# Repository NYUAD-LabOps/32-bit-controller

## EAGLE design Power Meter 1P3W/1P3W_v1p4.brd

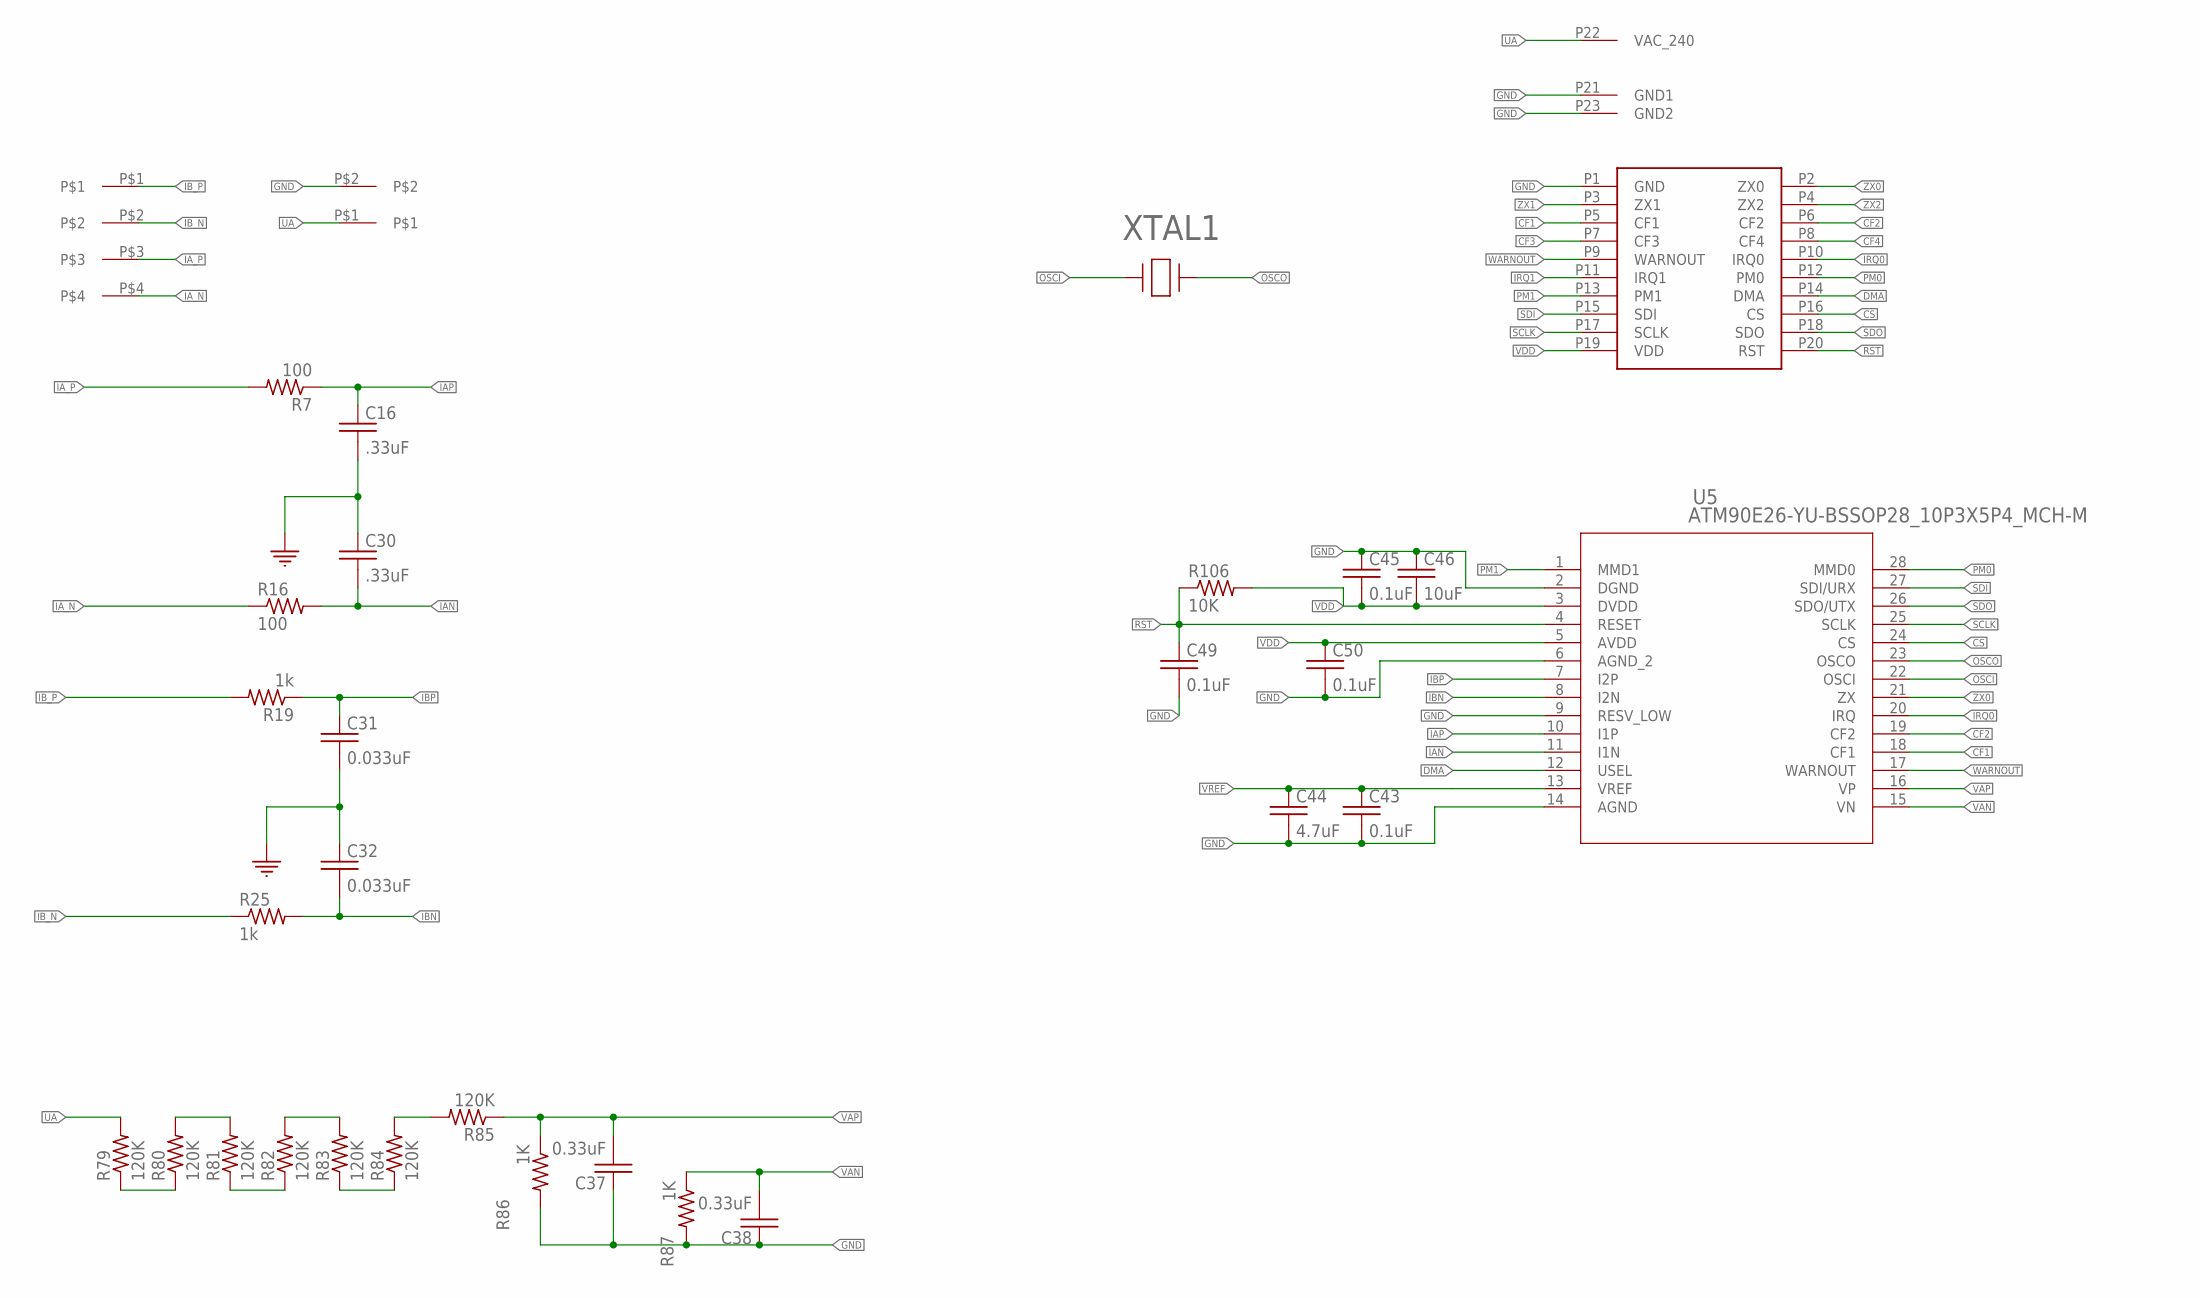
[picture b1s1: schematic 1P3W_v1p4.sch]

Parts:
C16, C30: .33uF; 0402
C31, C32: 0.033uF; 0402
C37, C38: 0.33uF; 0402
C43, C45, C49, C50: 0.1uF; 0402
C44: 4.7uF; 0402
C46: 10uF; 0402
J2: 3.81MM_1_X_4_RT_ANGLE_PLUG_HEADER; 1X4_3.81MM_PITCH
J3: 3.81MM_1_X_2_RT_ANGLE_PLUG_HEADER; 2_3.81MM_PITCH
R7, R16: 100; 0402
R19, R25: 1k; 0402
R79, R80, R81, R82, R83, R84, R85: 120K; 0402
R86, R87: 1K; 0402
R106: 10K; 0402
U5: ATM90E26-YU-BSSOP28_10P3X5P4_MCH-M; SSOP28_10P3X5P4_MCH-M
U$1: METER_BASE
XTAL1: ABLS-8.192MHZ-B2-TXTAL_HC/49US_ABLS_ABR-M; XTAL_HC/49US_ABLS_ABR-M

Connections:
CF1: U5.18 (CF1), U$1.P5 (CF1)
CF2: U5.19 (CF2), U$1.P6 (CF2)
CF3: U$1.P7 (CF3)
CF4: U$1.P8 (CF4)
CS: U5.24 (CS), U$1.P16 (CS)
DMA: U5.12 (USEL), U$1.P14 (DMA)
GND: C16.P$2 (2), C30.P$1 (1), C31.P$2 (2), C32.P$1 (1), C37.P$1 (1), C38.P$1 (1), C43.P$2 (2), C44.P$2 (2), C45.P$1 (1), C46.P$1 (1), C49.P$2 (2), C50.P$2 (2), J3.P$2, R86.P$2 (2), R87.P$2 (2), U5.2 (DGND), U5.6 (AGND_2), U5.9 (RESV_LOW), U5.14 (AGND), U$1.P1 (GND), U$1.P21 (GND1), U$1.P23 (GND2)
IAN: C30.P$2 (2), R16.P$2 (2), U5.11 (I1N)
IAP: C16.P$1 (1), R7.P$1 (1), U5.10 (I1P)
IA_N: J2.P$4, R16.P$1 (1)
IA_P: J2.P$3, R7.P$2 (2)
IBN: C32.P$2 (2), R25.P$2 (2), U5.8 (I2N)
IBP: C31.P$1 (1), R19.P$1 (1), U5.7 (I2P)
IB_N: J2.P$2, R25.P$1 (1)
IB_P: J2.P$1, R19.P$2 (2)
IRQ0: U5.20 (IRQ), U$1.P10 (IRQ0)
IRQ1: U$1.P11 (IRQ1)
unnamed: R79.P$1 (1), R80.P$1 (1)
unnamed: R80.P$2 (2), R81.P$2 (2)
unnamed: R81.P$1 (1), R82.P$1 (1)
unnamed: R82.P$2 (2), R83.P$2 (2)
unnamed: R83.P$1 (1), R84.P$1 (1)
unnamed: R84.P$2 (2), R85.P$2 (2)
OSCI: U5.22 (OSCI), XTAL1.1
OSCO: U5.23 (OSCO), XTAL1.2
PM0: U5.28 (MMD0), U$1.P12 (PM0)
PM1: U5.1 (MMD1), U$1.P13 (PM1)
RST: C49.P$1 (1), R106.P$1 (1), U5.4 (RESET), U$1.P20 (RST)
SCLK: U5.25 (SCLK), U$1.P17 (SCLK)
SDI: U5.27 (SDI/URX), U$1.P15 (SDI)
SDO: U5.26 (SDO/UTX), U$1.P18 (SDO)
UA: J3.P$1, R79.P$2 (2), U$1.P22 (VAC_240)
VAN: C38.P$2 (2), R87.P$1 (1), U5.15 (VN)
VAP: C37.P$2 (2), R85.P$1 (1), R86.P$1 (1), U5.16 (VP)
VDD: C45.P$2 (2), C46.P$2 (2), C50.P$1 (1), R106.P$2 (2), U5.3 (DVDD), U5.5 (AVDD), U$1.P19 (VDD)
VREF: C43.P$1 (1), C44.P$1 (1), U5.13 (VREF)
WARNOUT: U5.17 (WARNOUT), U$1.P9 (WARNOUT)
ZX0: U5.21 (ZX), U$1.P2 (ZX0)
ZX1: U$1.P3 (ZX1)
ZX2: U$1.P4 (ZX2)

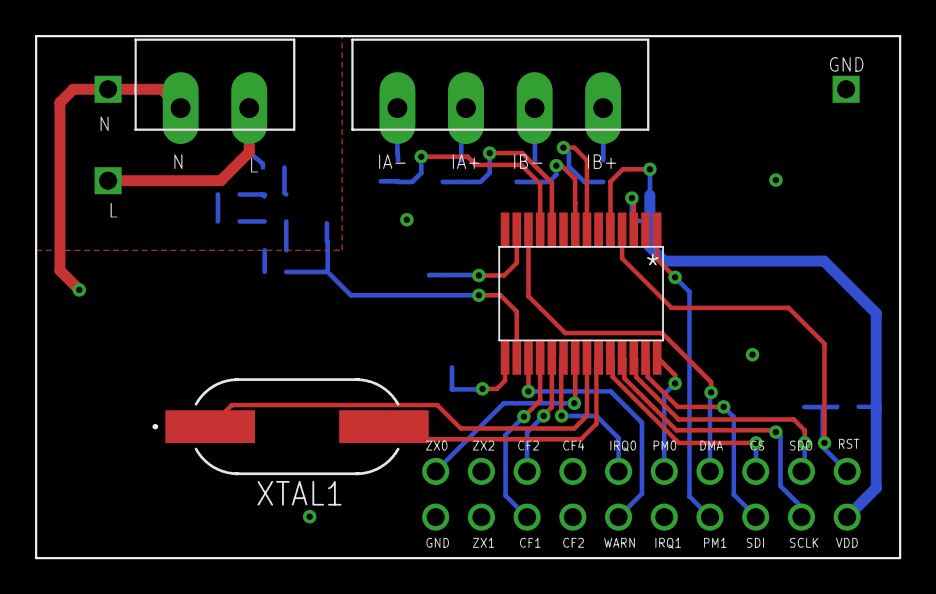
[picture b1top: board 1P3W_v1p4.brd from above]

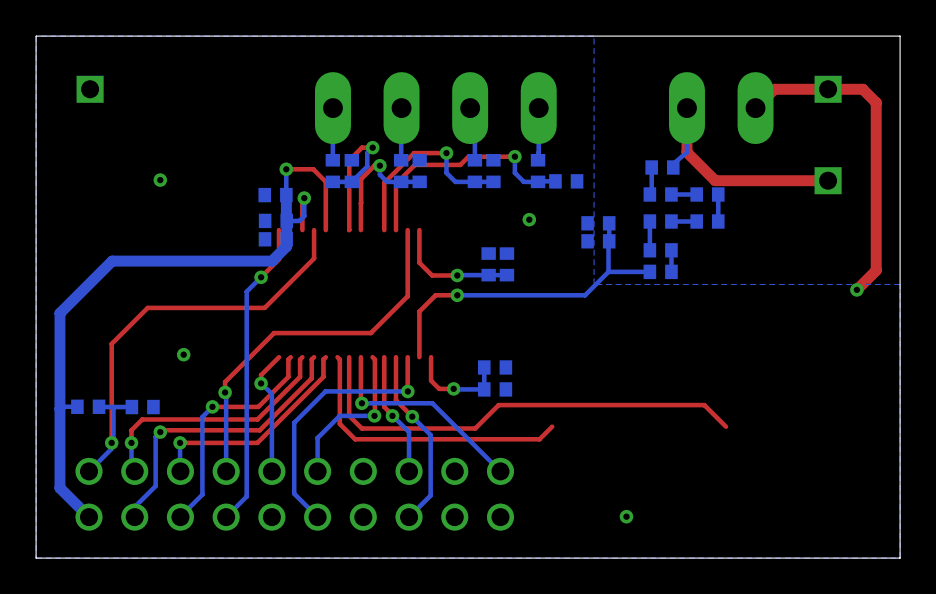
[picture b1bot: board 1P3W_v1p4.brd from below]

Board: 2 copper layers, 48.0 x 29.0 mm, 31 parts (26 on the bottom side), 35 nets.

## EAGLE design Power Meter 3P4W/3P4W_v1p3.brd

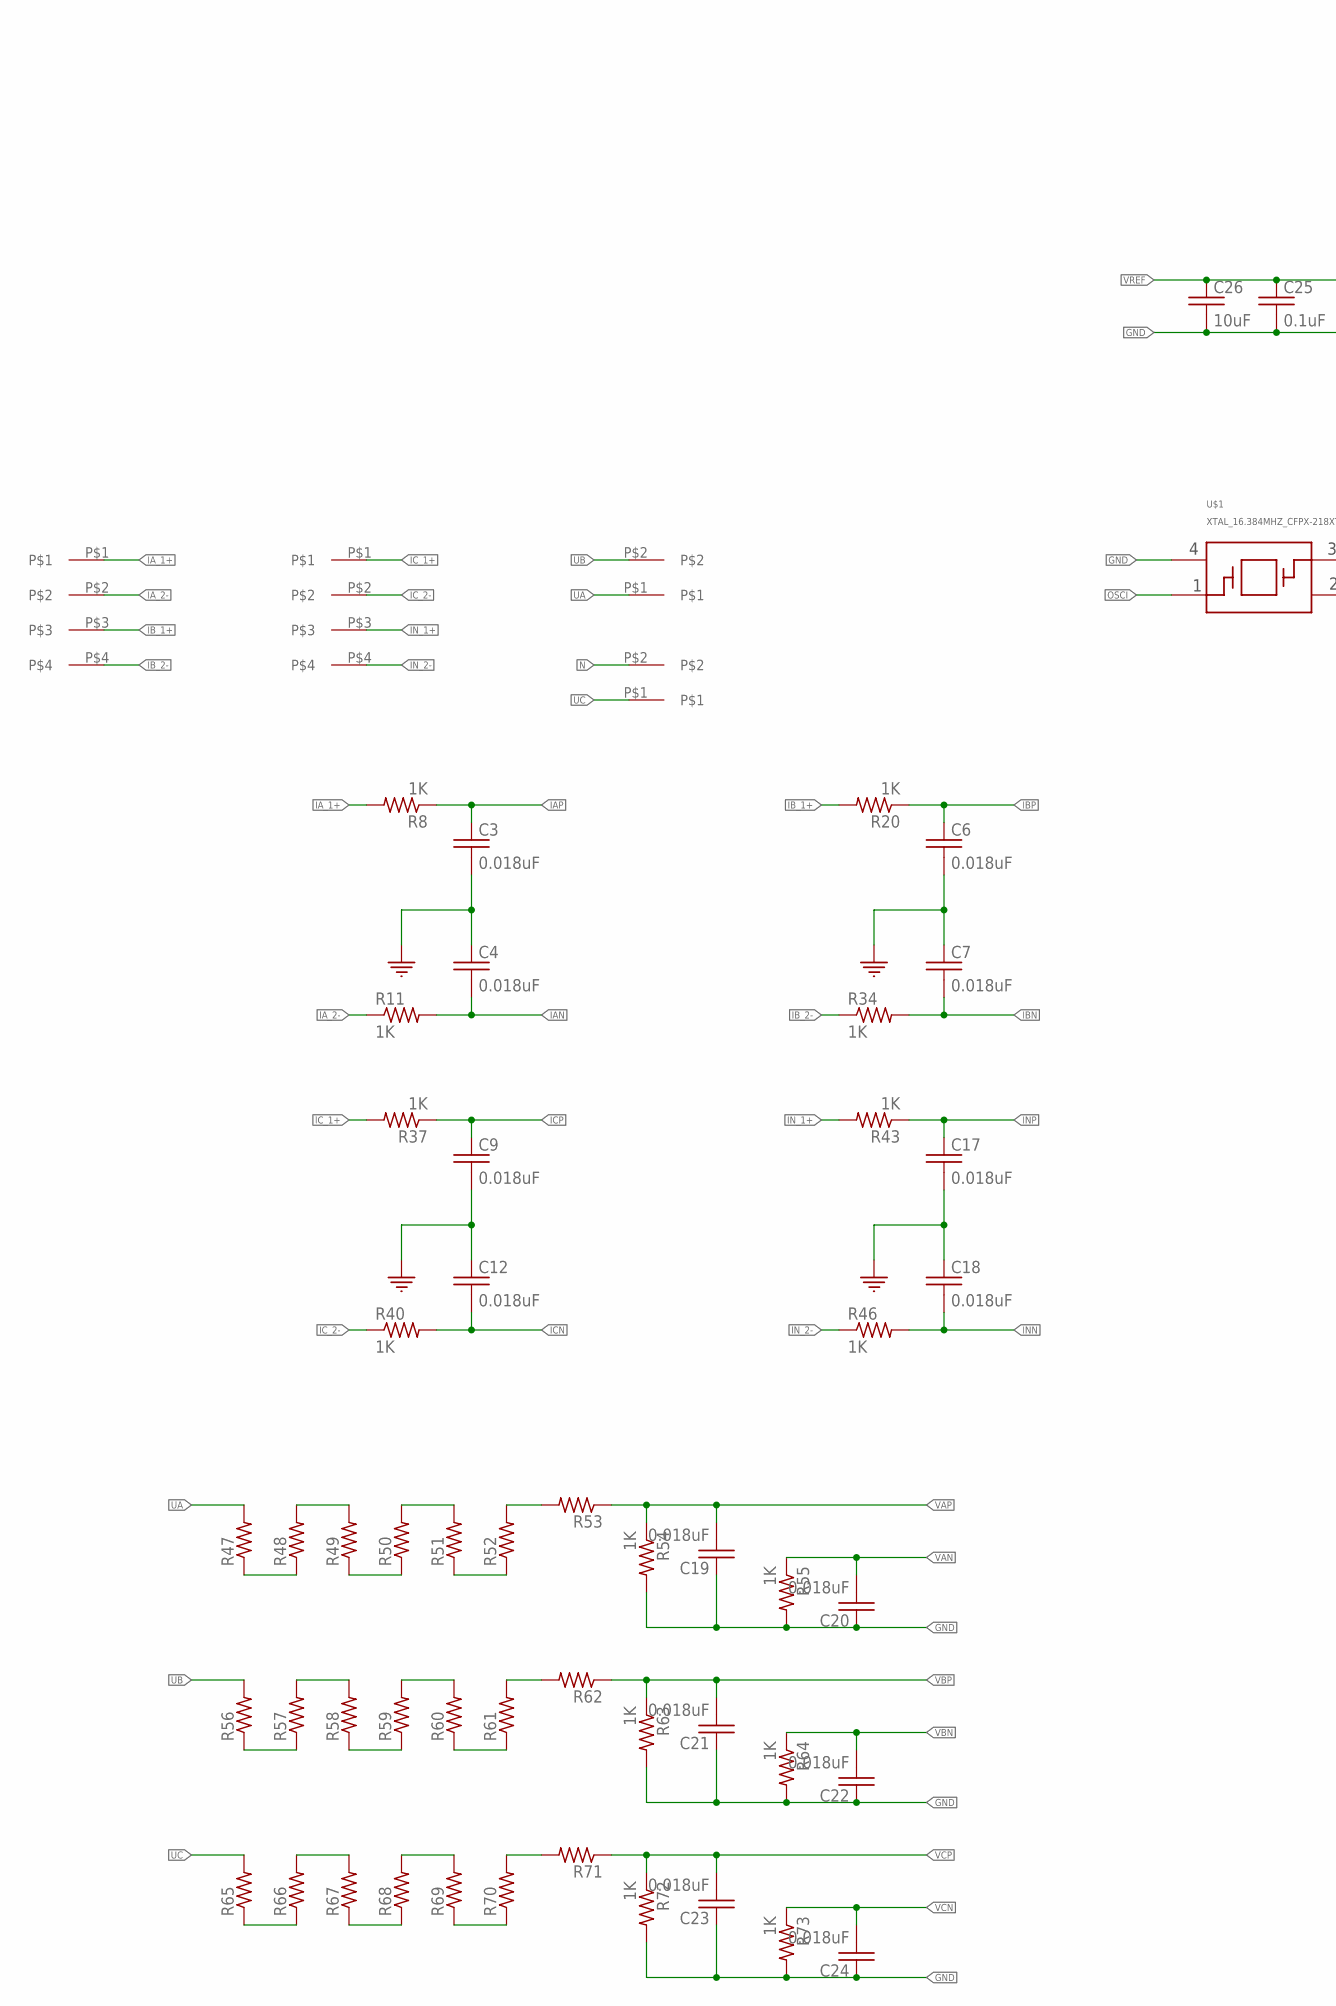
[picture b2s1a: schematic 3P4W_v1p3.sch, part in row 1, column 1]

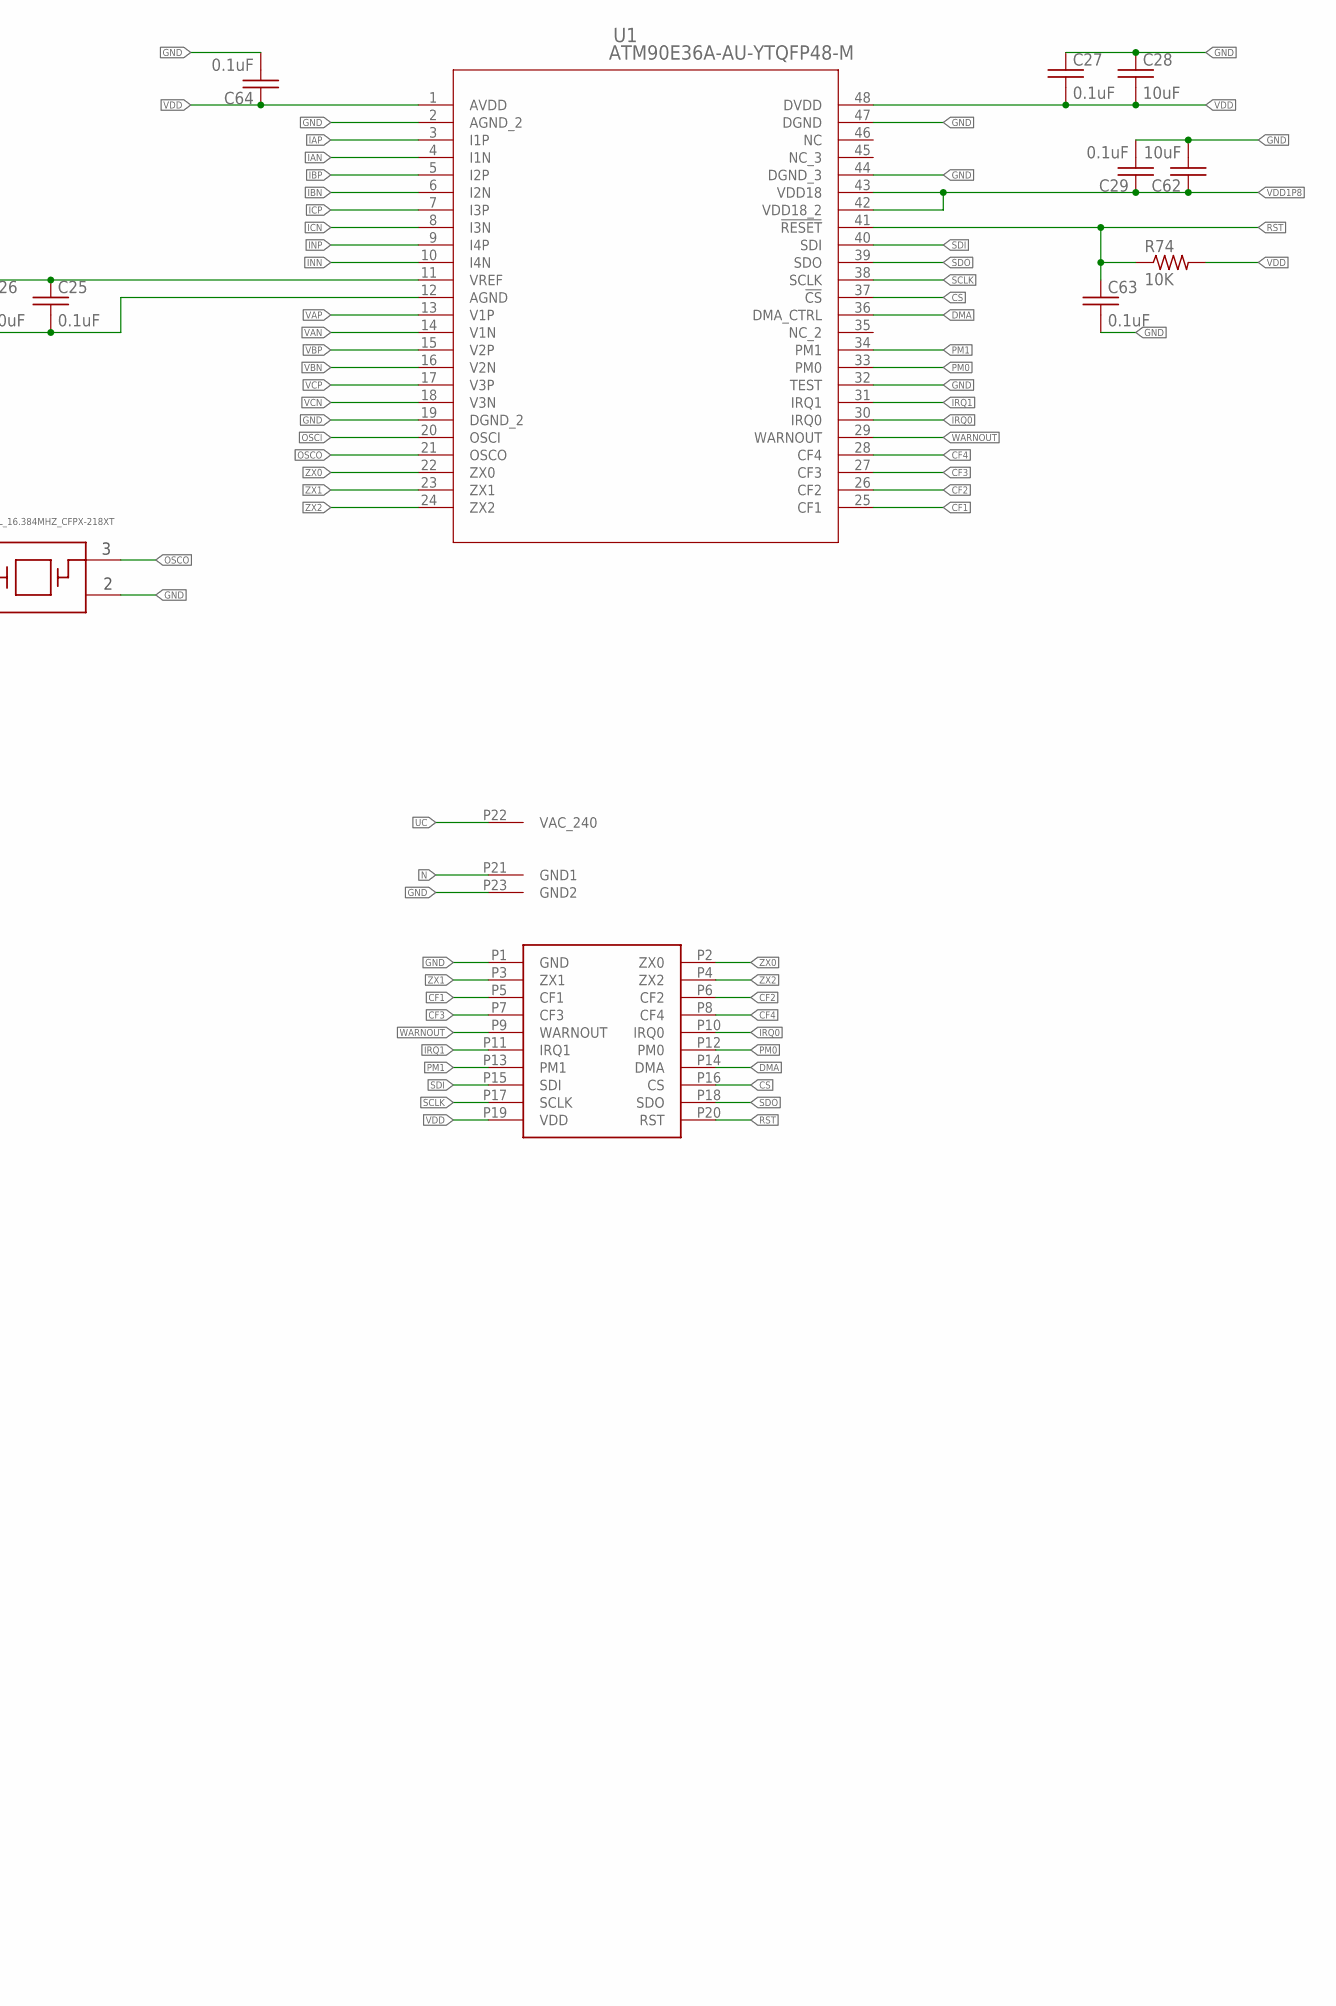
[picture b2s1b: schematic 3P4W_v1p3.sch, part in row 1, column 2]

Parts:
C3, C4, C6, C7, C9, C12, C17, C18, C19, C20, C21, C22, C23, C24: 0.018uF; 0402
C25, C27, C29, C63, C64: 0.1uF; 0402
C26, C28, C62: 10uF; 0402
J6, J7: 3.81MM_1_X_2_RT_ANGLE_PLUG_HEADER; 2_3.81MM_PITCH
J13, J14: 3.81MM_1_X_4_RT_ANGLE_PLUG_HEADER; 1X4_3.81MM_PITCH
R8, R11, R20, R34, R37, R40, R43, R46, R54, R55, R63, R64, R72, R73: 1K; 0402
R47, R48, R49, R50, R51, R52, R53, R56, R57, R58, R59, R60, R61, R62, R65, R66, R67, R68, R69, R70, R71: R_0402; 0402
R74: 10K; 0402
U1: ATM90E36A-AU-YTQFP48-M; TQFP48-M
U$1: XTAL_16.384MHZ_CFPX-218XT; XTAL_2.5X2.0
U$2: METER_BASE

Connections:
CF1: U1.25 (CF1), U$2.P5 (CF1)
CF2: U1.26 (CF2), U$2.P6 (CF2)
CF3: U1.27 (CF3), U$2.P7 (CF3)
CF4: U1.28 (CF4), U$2.P8 (CF4)
CS: U1.37 (!CS), U$2.P16 (CS)
DMA: U1.36 (DMA_CTRL), U$2.P14 (DMA)
GND: C3.P$2 (2), C4.P$1 (1), C6.P$2 (2), C7.P$1 (1), C9.P$2 (2), C12.P$1 (1), C17.P$2 (2), C18.P$1 (1), C19.P$1 (1), C20.P$1 (1), C21.P$1 (1), C22.P$1 (1), C23.P$1 (1), C24.P$1 (1), C25.P$2 (2), C26.P$2 (2), C27.P$1 (1), C28.P$1 (1), C29.P$2 (2), C62.P$2 (2), C63.P$2 (2), C64.P$2 (2), R54.P$2 (2), R55.P$2 (2), R63.P$2 (2), R64.P$2 (2), R72.P$2 (2), R73.P$2 (2), U1.2 (AGND_2), U1.12 (AGND), U1.19 (DGND_2), U1.32 (TEST), U1.44 (DGND_3), U1.47 (DGND), U$1.2, U$1.4, U$2.P1 (GND), U$2.P23 (GND2)
IAN: C4.P$2 (2), R11.P$2 (2), U1.4 (I1N)
IAP: C3.P$1 (1), R8.P$1 (1), U1.3 (I1P)
IA_1+: J13.P$1, R8.P$2 (2)
IA_2-: J13.P$2, R11.P$1 (1)
IBN: C7.P$2 (2), R34.P$2 (2), U1.6 (I2N)
IBP: C6.P$1 (1), R20.P$1 (1), U1.5 (I2P)
IB_1+: J13.P$3, R20.P$2 (2)
IB_2-: J13.P$4, R34.P$1 (1)
ICN: C12.P$2 (2), R40.P$2 (2), U1.8 (I3N)
ICP: C9.P$1 (1), R37.P$1 (1), U1.7 (I3P)
IC_1+: J14.P$1, R37.P$2 (2)
IC_2-: J14.P$2, R40.P$1 (1)
INN: C18.P$2 (2), R46.P$2 (2), U1.10 (I4N)
INP: C17.P$1 (1), R43.P$1 (1), U1.9 (I4P)
IN_1+: J14.P$3, R43.P$2 (2)
IN_2-: J14.P$4, R46.P$1 (1)
IRQ0: U1.30 (IRQ0), U$2.P10 (IRQ0)
IRQ1: U1.31 (IRQ1), U$2.P11 (IRQ1)
N: J7.P$2, U$2.P21 (GND1)
unnamed: R56.P$1 (1), R57.P$1 (1)
unnamed: R47.P$1 (1), R48.P$1 (1)
unnamed: R48.P$2 (2), R49.P$2 (2)
unnamed: R49.P$1 (1), R50.P$1 (1)
unnamed: R50.P$2 (2), R51.P$2 (2)
unnamed: R51.P$1 (1), R52.P$1 (1)
unnamed: R52.P$2 (2), R53.P$2 (2)
unnamed: R57.P$2 (2), R58.P$2 (2)
unnamed: R58.P$1 (1), R59.P$1 (1)
unnamed: R59.P$2 (2), R60.P$2 (2)
unnamed: R60.P$1 (1), R61.P$1 (1)
unnamed: R61.P$2 (2), R62.P$2 (2)
unnamed: R65.P$1 (1), R66.P$1 (1)
unnamed: R66.P$2 (2), R67.P$2 (2)
unnamed: R67.P$1 (1), R68.P$1 (1)
unnamed: R68.P$2 (2), R69.P$2 (2)
unnamed: R69.P$1 (1), R70.P$1 (1)
unnamed: R70.P$2 (2), R71.P$2 (2)
OSCI: U1.20 (OSCI), U$1.1
OSCO: U1.21 (OSCO), U$1.3
PM0: U1.33 (PM0), U$2.P12 (PM0)
PM1: U1.34 (PM1), U$2.P13 (PM1)
RST: C63.P$1 (1), R74.P$1 (1), U1.41 (!RESET), U$2.P20 (RST)
SCLK: U1.38 (SCLK), U$2.P17 (SCLK)
SDI: U1.40 (SDI), U$2.P15 (SDI)
SDO: U1.39 (SDO), U$2.P18 (SDO)
UA: J6.P$1, R47.P$2 (2)
UB: J6.P$2, R56.P$2 (2)
UC: J7.P$1, R65.P$2 (2), U$2.P22 (VAC_240)
VAN: C20.P$2 (2), R55.P$1 (1), U1.14 (V1N)
VAP: C19.P$2 (2), R53.P$1 (1), R54.P$1 (1), U1.13 (V1P)
VBN: C22.P$2 (2), R64.P$1 (1), U1.16 (V2N)
VBP: C21.P$2 (2), R62.P$1 (1), R63.P$1 (1), U1.15 (V2P)
VCN: C24.P$2 (2), R73.P$1 (1), U1.18 (V3N)
VCP: C23.P$2 (2), R71.P$1 (1), R72.P$1 (1), U1.17 (V3P)
VDD: C27.P$2 (2), C28.P$2 (2), C64.P$1 (1), R74.P$2 (2), U1.1 (AVDD), U1.48 (DVDD), U$2.P19 (VDD)
VDD1P8: C29.P$1 (1), C62.P$1 (1), U1.42 (VDD18_2), U1.43 (VDD18)
VREF: C25.P$1 (1), C26.P$1 (1), U1.11 (VREF)
WARNOUT: U1.29 (WARNOUT), U$2.P9 (WARNOUT)
ZX0: U1.22 (ZX0), U$2.P2 (ZX0)
ZX1: U1.23 (ZX1), U$2.P3 (ZX1)
ZX2: U1.24 (ZX2), U$2.P4 (ZX2)

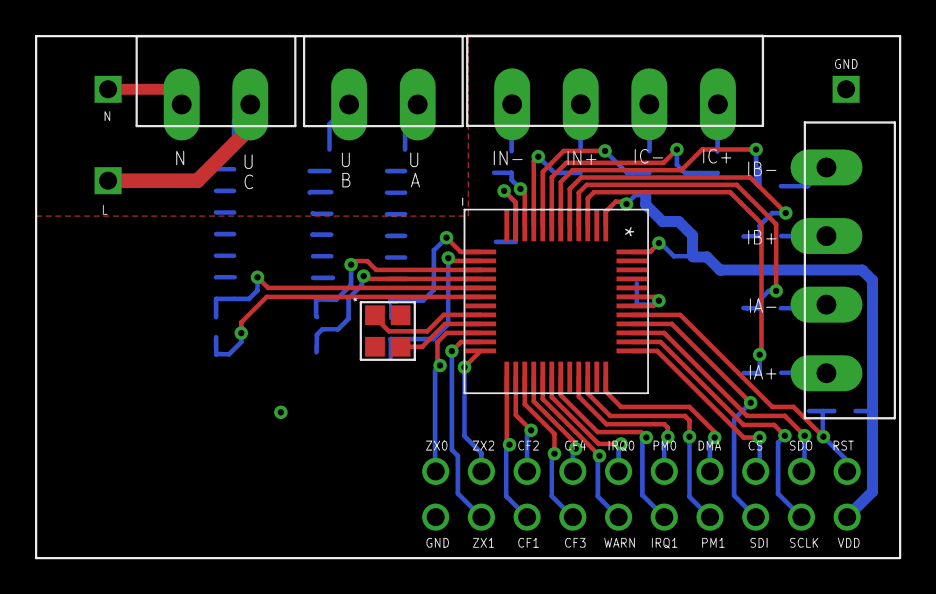
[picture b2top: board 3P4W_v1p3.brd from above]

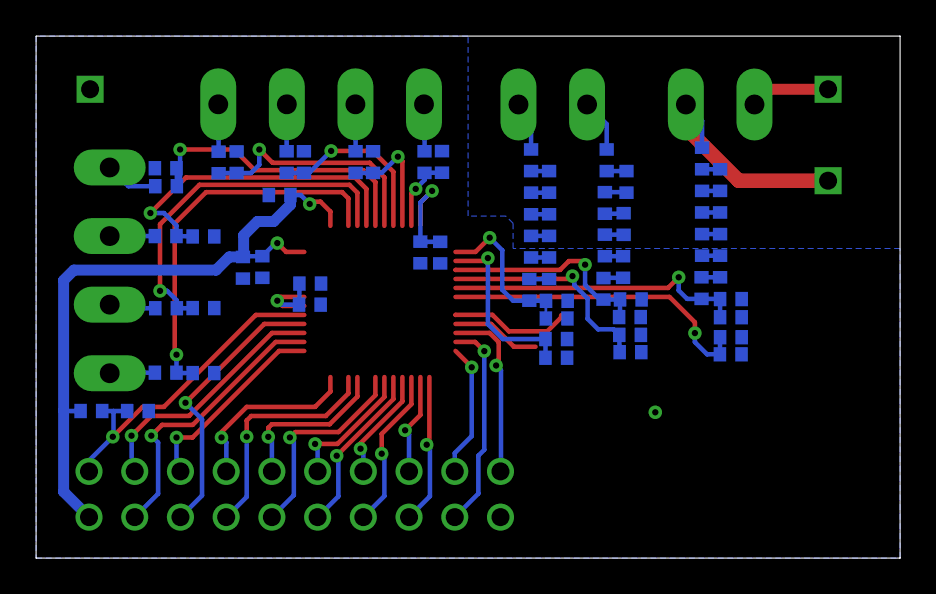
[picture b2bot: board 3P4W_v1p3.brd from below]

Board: 2 copper layers, 48.0 x 29.0 mm, 65 parts (58 on the bottom side), 68 nets.

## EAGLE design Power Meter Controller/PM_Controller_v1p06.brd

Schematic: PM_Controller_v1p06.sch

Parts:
C1, C3, C4, C6, C7, C8, C10, C11, C13, C14, C16, C17, C18, C19, C22, C24, C25, C27, C30, C31, C34, C35, C36, C37, C38, C39, C40, C44, C46, C49, C54, C55, C56, C58, C59, C60, C61, C62: 0.1uF; 0402
C2, C32, C65: 1uF; 0402
C5, C21, C29, C57, C63, C64: 10uF; 0402
C12, C33: 1.0 uF; 0402
C15: 100uF; C1210
C20: CAP_THIN_FILM_TDK_32922CAP; CAP_THIN_FILM_32922
C23, C26, C28: 22uF; C1206
C41, C42: 24pF; 0402
C43, C48: 22uF; 0603
C45: 2.2uF; 0402
C47: 100pF; 0402
C50, C51: 12pF; 0402
C52, C53: 18pF; 0402
FB2/2: FB_0805_120_OHM; 0805
IC3: LT1129CST5; SOT223
IC4: LT1129CST3; SOT223
J1: 2_X_10_HEADER_GENERIC; 2_X_10_.1_INCH
J2: USB_MICRO-B
J3: USB_A; USB_A_SMT
J4: RJ45_WITH_ELEC; RJ45_TH_ELEC
J6, J7: 3.81MM_1_X_2_RT_ANGLE_PLUG_HEADER; 2_3.81MM_PITCH
J11: CONN_05X2PTH; 2X5
J12: PI3_HEADER; HEADER_2_X_20_.1_INCH
LED1, LED3, LED4: LED_0805_GREEN
R1, R12: 10K0; 0402
R2, R3, R5, R6: 24R0; 0402
R4, R16, R17, R18, R26, R27: 10K; 0402
R7: 15K0; 0402
R8, R9: 501; 0402
R10: R_0402; 0402
R11, R13, R15, R20: 100; 0402
R14, R21: 1M; 0402
R19: 2.2K; 0402
R23, R24: 470; 0402
R25: 6k49; 0402
R28, R29: 1K50; 0402
R30, R31, R32, R33: 33; 0402
R34: 30K0; 0402
U1: ADUM3160BRWZ-RLRW_16_ADI-M; RW_16_ADI-M
U2: AP2141DWG-5; SOT-23-5
U3: KSZ8081RNACAQFN-24-M; QFN-24-M
U4: S7G2LQFP176; LQFP176_24X24
U5: TMLM_04109; TMLM04
U6, U7: AD8495ARMZ; RM_8_ADI
U$2: METER_BASE
U$3: XTAL_25_MHZ; SMD_3225
U$4: 10uF; 0402
U$7: VAR_10MM_VDRUS10
U$8: 220uF; C_AL_ELECTROLYTIC_SMD_220UF
X3: 32.768KHZ; SMD_X_2_PADS
X4: 24MHZ; SMD_3225

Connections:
1_IN+: C12.P$2 (2), C18.P$1 (1), R11.P$2 (2), U6.8 (+IN)
1_IN-: C12.P$1 (1), C17.P$2 (2), R13.P$2 (2), U6.1 (IN-)
1_RED-: J6.P$2, R13.P$1 (1), R14.P$2 (2)
1_V_KT: U4.169 (P0_0/AN0\00), U6.5 (SENSE), U6.6 (OUT)
1_YLW+: J6.P$1, R11.P$1 (1)
2_IN+: C33.P$2 (2), C35.P$1 (1), R15.P$2 (2), U7.8 (+IN)
2_IN-: C33.P$1 (1), C34.P$2 (2), R20.P$2 (2), U7.1 (IN-)
2_RED-: J7.P$2, R20.P$1 (1), R21.P$2 (2)
2_V_KT: U4.168 (P0_1/AN001), U7.5 (SENSE), U7.6 (OUT)
2_YLW+: J7.P$1, R15.P$1 (1)
C58: C39.P$1 (1), J4.4 (CT1)
C60: C40.P$1 (1), J4.5 (CT2)
CF1: U4.164 (P0_5/AN101), U$2.P5 (CF1)
CF2: U4.163 (P0_6/AN102), U$2.P6 (CF2)
CF3: U4.161 (P0_8/AN003), U$2.P7 (CF3)
CF4: U4.160 (P0_9/AN004), U$2.P8 (CF4)
CRS_DV: R33.P$2 (2), U3.15 (CRS_DV/PHYAD[1:0])
D-: R5.P$2 (2), U1.11 (DD)
DMA: U4.122 (P6_0), U$2.P14 (DMA)
ETH: U3.16 (REF_CLK), U4.9 (P7_1)
ETH_CRS_DV: R33.P$1 (1), U4.13 (P7_5)
ETH_IRQ14: R26.P$1 (1), U3.18 (INTRP), U4.159 (P0_10/AN103)
ETH_MDC: R28.P$1 (1), U3.11 (MDC), U4.4 (P4_3)
ETH_MDIO: R29.P$1 (1), U3.10 (MDIO), U4.5 (P4_4)
ETH_RESET: R27.P$1 (1), U3.24 (!RST), U4.172 (P8_6), U$4.P$1 (1)
ETH_RXD0: R31.P$1 (1), U4.10 (P7_2)
ETH_RXD1: R30.P$1 (1), U4.11 (P7_3)
ETH_RX_ER: R32.P$1 (1), U4.12 (P7_4)
ETH_TXD0: U3.20 (TXD0), U4.8 (P7_0)
ETH_TXD1: U3.21 (TXD1), U4.7 (P4_6)
ETH_TXD_EN: U3.19 (TXEN), U4.6 (P4_5)
GND: C1.P$1 (1), C2.P$1 (1), C5.P$2 (2), C6.P$1 (1), C7.P$1 (1), C8.P$2 (2), C10.P$1 (1), C11.P$2 (2), C13.P$1 (1), C14.P$1 (1), C15.2, C16.P$1 (1), C17.P$1 (1), C18.P$2 (2), C19.P$2 (2), C20.P$2, C21.P$2 (2), C22.P$2 (2), C23.2, C24.P$2 (2), C25.P$2 (2), C26.2, C27.P$2 (2), C28.2, C29.P$2 (2), C30.P$1 (1), C31.P$2 (2), C32.P$2 (2), C34.P$1 (1), C35.P$2 (2), C36.P$1 (1), C37.P$1 (1), C38.P$2 (2), C39.P$2 (2), C40.P$2 (2), C41.P$2 (2), C42.P$2 (2), C43.2, C44.P$2 (2), C45.P$2 (2), C46.P$2 (2), C47.P$2 (2), C48.2, C49.P$2 (2), C50.P$2 (2), C51.P$2 (2), C52.P$2 (2), C53.P$2 (2), C54.P$1 (1), C55.P$1 (1), C56.P$1 (1), C57.P$2 (2), C58.P$2 (2), C59.P$2 (2), C60.P$2 (2), C61.P$1 (1), C62.P$2 (2), C63.P$2 (2), C64.P$1 (1), C65.P$2 (2), IC3.2 (GND), IC3.4 (GND), IC4.2 (GND), IC4.4 (GND), J1.P$19, J3.GND, J4.8, J4.10 (GLO), J11.6, J11.8, J11.10, J12.P$6 (GND), J12.P$9 (GND), J12.P$14 (GND), J12.P$20 (GND), J12.P$25 (GND), J12.P$30 (GND), J12.P$34 (GND), J12.P$39 (GND), LED3.C, LED4.C, R4.P$2 (2), R14.P$1 (1), R16.P$1 (1), R17.P$1 (1), R19.P$1 (1), R21.P$1 (1), R25.P$1 (1), R34.P$1 (1), U1.9 (!_4), U1.15 (!), U2.2 (GND), U3.22 (GND), U3.25, U4.22 (VSS1), U4.28 (AVSS_USBHS), U4.29 (PVSS_USBHS), U4.30 (VSS2_USBHS), U4.33 (VSS1_USBHS), U4.35 (VSSIO), U4.45 (VSS_USB), U4.60 (VSS(IO)2), U4.63 (VSS(IO/DCDC)), U4.66 (VCC_DCDC(IO/DCDC)), U4.83 (VSS(IO)3), U4.98 (VSS(IO)4), U4.111 (VSS(IO)5), U4.124 (VSS(IO)6), U4.139 (VSS(IO)7), U4.150 (VSS(IO)8), U4.153 (VREFL), U4.156 (AVSS0), U4.157 (VREFL0), U4.170 (VSS(IO)9), U5.P$3 (VOUT-), U5.P$6 (AC_N), U6.2 (REF), U6.3 (VS-), U7.2 (REF), U7.3 (VS-), U$2.P1 (GND), U$2.P21 (GND1), U$2.P23 (GND2), U$3.2, U$3.4, U$4.P$2 (2), U$7.P$2, U$8.N- (-), X4.2, X4.4
GND2: C3.P$2 (2), C4.P$2 (2), J2.P$5 (GND), LED1.C, U1.2 (!_2), U1.8 (!_3)
GNDE: C16.P$2 (2), C64.P$2 (2), J2.P$6 (SHIELD1), J2.P$7 (SHIELD2), J2.P$8 (SHIELD3), J2.P$9 (SHIELD4), J3.SHLD1 (SHIELD_1), J3.SHLD2 (SHIELD_2), J4.13 (GNDE0), J4.14 (GNDE1), R4.P$1 (1)
GP4: J12.P$7 (GP4), U4.49 (P2_7)
GP5: J12.P$29 (GP5), U4.57 (P3_15)
GP6: J12.P$31 (GP6), U4.59 (P9_1)
GP12: J12.P$32 (GP12), U4.58 (P9_0)
GP13: J12.P$33 (GP13), U4.76 (P3_10)
GP14: J12.P$8 (TXO), U4.42 (P4_9)
GP15: J12.P$10 (RXI), U4.43 (P4_8)
GP16: J12.P$36 (GP16), U4.79 (P3_7)
GP17: J12.P$11 (GP17), U4.51 (P2_5)
GP18: J12.P$12 (GP18#), U4.50 (P2_6)
GP19: J12.P$35 (GP19), U4.77 (P3_9)
GP20: J12.P$38 (GP20), U4.81 (P3_5)
GP21: J12.P$40 (GP21), U4.82 (P3_4)
GP22: J12.P$15 (GP22), U4.72 (P9_6)
GP23: J12.P$16 (GP23), U4.71 (P9_7)
GP24: J12.P$18 (GP24), U4.73 (P9_5)
GP25: J12.P$22 (GP25), U4.56 (P3_14)
GP26: J12.P$37 (GP26), U4.80 (P3_6)
GP27: J12.P$13 (GP27), U4.70 (P9_8)
ID_SC: J12.P$28 (ID_SC), U4.93 (P1_12)
ID_SD: J12.P$27 (ID_SD), U4.92 (P1_11)
IIC_0_SCL: J12.P$5 (SCL), U4.1 (P4_0)
IIC_0_SDA: J12.P$3 (SDA), U4.2 (P4_1)
IRQ0: U4.86 (P3_2), U$2.P10 (IRQ0)
IRQ1: U4.87 (P3_1), U$2.P11 (IRQ1)
LED1/SPEED: J4.11 (YLO), U3.23 (LED0/ANEN_SPEED)
M0_STEP: U4.16 (PB_0)
unnamed: C37.P$2 (2), U4.148 (VCL2)
unnamed: J2.P$2 (D-), R3.P$2 (2)
unnamed: R2.P$1 (1), U1.7 (UD+)
unnamed: C38.P$1 (1), U4.19 (VCLO)
unnamed: C31.P$1 (1), U4.62 (VCL1)
unnamed: R17.P$2 (2), U4.64 (VLO1(DCDC))
unnamed: R16.P$2 (2), U4.65 (VLO2(DCDC))
unnamed: R19.P$2 (2), U4.27 (USBHS_RREF)
unnamed: LED3.A, R8.P$2 (2)
unnamed: LED4.A, R9.P$2 (2)
unnamed: LED1.A, R10.P$1 (1)
unnamed: R3.P$1 (1), U1.6 (UD)
unnamed: J2.P$3 (D+), R2.P$2 (2)
unnamed: C3.P$1 (1), U1.3 (VDD1), U1.4 (PDEN), U1.5 (SPU)
unnamed: C7.P$2 (2), U1.12 (PIN), U1.13 (SPD), U1.14 (VDD2)
unnamed: R6.P$2 (2), U1.10 (DD+)
NC: J4.7
P0_02: J1.P$6, U4.167 (P0_2/AN002)
P0_03: J1.P$5, U4.166 (P0_3/PGAVSS000)
P0_04: J1.P$8, U4.165 (P0_4/AN100)
P0_07: J1.P$7, U4.162 (P0_7/PGVSS100)
P0_14: J1.P$10, U4.152 (P0_14/DA0/AN005/AN105)
P0_15: J1.P$9, U4.151 (P0_15/DA1/AN006/AN106)
P1_05: U4.127 (P1_5)
P1_13: U4.94 (P1_13)
P1_14: U4.95 (P1_14)
P1_15: U4.96 (P1_15)
P2_00: U4.69 (P2_0(INPUT_ONLY))
P2_01: U4.68 (P2_1/MD)
P3_03: U4.85 (P3_3)
P3_11: U4.75 (P3_11)
P4_02: U4.3 (P4_2)
P4_10: U4.41 (P4_10)
P4_11: U4.40 (P4_11)
P4_12: U4.39 (P4_12)
P4_13: U4.38 (P4_13)
P4_14: U4.37 (P4_14)
P4_15: U4.36 (P4_15)
P5_00: J1.P$17, U4.140 (P5_0/AN016)
P5_01: J1.P$18, U4.141 (P5_1/AN116)
P5_02: J1.P$15, U4.142 (P5_2/AN017)
P5_03: J1.P$16, U4.143 (P5_3/AN117)
P5_04: J1.P$13, U4.144 (P5_4/AN018)
P5_05: J1.P$14, U4.145 (P5_5/AN118)
P5_06: J1.P$11, U4.146 (P5_6/AN019)
P5_07: J1.P$12, U4.147 (P5_7/AN119)
P5_11: J1.P$2, U4.176 (P5_11)
P5_12: J1.P$1, U4.175 (P5_12)
P5_13: J1.P$4, U4.174 (P5_13)
P6_02: U4.120 (P6_2)
P6_03: U4.119 (P6_3)
P6_04: U4.118 (P6_4)
P6_05: U4.117 (P6_5)
P6_06: U4.116 (P6_6)
P6_07: U4.115 (P6_7)
P6_08: U4.99 (P6_8)
P6_09: U4.100 (P6_9)
P6_10: U4.101 (P6_10)
P6_11: U4.102 (P6_11)
P6_12: U4.103 (P6_12)
P6_13: U4.104 (P6_13)
P6_14: U4.105 (P6_14)
P6_15: U4.106 (P6_15)
P7_06: U4.14 (P7_6)
P7_07: U4.15 (P7_7)
P8_03: U4.136 (P8_3)
P8_04: U4.137 (P8_4)
P8_05: J1.P$3, U4.173 (P8_5)
PA_00: U4.114 (PA_0)
PA_01: U4.113 (PA_1)
PA_08: U4.107 (PA_8)
PA_09: U4.108 (PA_9)
PA_10: U4.109 (PA_10)
PM0: U4.126 (P1_6), U$2.P12 (PM0)
PM1: U4.125 (P1_7), U$2.P13 (PM1)
R51: J4.12 (YHI), R23.P$1 (1)
R52: J4.9 (GHI), R24.P$1 (1)
RESET: C57.P$1 (1), J11.9, R18.P$1 (1), U4.67 (RES#)
REXT: C47.P$1 (1), R25.P$2 (2), U3.9 (REXT)
RST: U4.121 (P6_1), U$2.P20 (RST)
RXD0: R31.P$2 (2), U3.13 (RXD0)
RXD1: R30.P$2 (2), U3.12 (RXD1)
RXER: R32.P$2 (2), U3.17 (RXER)
RXM: J4.6 (RD-), U3.3 (RXM)
RXP: J4.3 (RD+), U3.4 (RXP)
SPI_0_CS_0: U4.129 (P1_3), U$2.P16 (CS)
SPI_0_MISO: U4.132 (P1_0), U$2.P18 (SDO)
SPI_0_MOSI: U4.131 (P1_1), U$2.P15 (SDI)
SPI_0_SCLK: U4.130 (P1_2), U$2.P17 (SCLK)
SPI_1_CS_0: J12.P$24 (CE0), U4.55 (P3_13)
SPI_1_CS_1: J12.P$26 (CE1), U4.74 (P3_12)
SPI_1_MISO: J12.P$21 (MISO), U4.54 (P2_2)
SPI_1_MOSI: J12.P$19 (MOSI), U4.53 (P2_3)
SPI_1_SCLK: J12.P$23 (SCLK), U4.52 (P2_4)
TCK: J11.7, U4.88 (P3_0)
TDI: J11.1, U4.91 (P1_10)
TDO: J11.3, U4.90 (P1_9)
TMS: J11.5, U4.89 (P1_8)
TXM: J4.2 (TD-), U3.5 (TXM)
TXP: J4.1 (TD+), U3.6 (TXP)
UC: C20.P$1, U5.P$5 (AC_L), U$2.P22 (VAC_240), U$7.P$1
USBHS_FAULT: R12.P$1 (1), U2.3 (FLG), U4.78 (P3_8)
USBHS_N: J3.D-, U4.31 (USBHS_DM)
USBHS_P: J3.D+, U4.32 (USBHS_DP)
USBHS_VBUS: C11.P$1 (1), C15.1, J3.VBUS, U2.5 (OUT), U4.17 (PB_1)
USBHS_VBUSEN: R1.P$1 (1), U2.1 (EN)
USB_N: R5.P$1 (1), U4.46 (USB_DM)
USB_P: R6.P$1 (1), U4.47 (USB_DP)
USB_VBUS: C4.P$1 (1), J2.P$1 (VBUS), R10.P$2 (2), U1.1 (VBUS1)
USB_VBUS_B: R7.P$1 (1), U4.44 (P4_7)
VCC: C21.P$1 (1), C22.P$1 (1), C23.1, C24.P$1 (1), IC3.1 (IN), IC4.1 (IN), U5.P$2 (VOUT+), U$8.P+ (+)
VCL_F(FLASH): C36.P$2 (2), U4.112 (VCL_F(FLASH))
VDD: C1.P$2 (2), C2.P$2 (2), C10.P$2 (2), C13.P$2 (2), C14.P$2 (2), C19.P$1 (1), C25.P$1 (1), C26.1, C29.P$1 (1), C30.P$2 (2), C32.P$1 (1), C48.1, C49.P$1 (1), C54.P$2 (2), C55.P$2 (2), C56.P$2 (2), C58.P$1 (1), C59.P$1 (1), C60.P$1 (1), C61.P$2 (2), C62.P$1 (1), C63.P$1 (1), FB2/2.1, IC4.3 (OUT), J1.P$20, J11.2, J11.4, J12.P$1 (3.3V), J12.P$17 (3.3V), R8.P$1 (1), R18.P$2 (2), R23.P$2 (2), R24.P$2 (2), R26.P$2 (2), R27.P$2 (2), R28.P$2 (2), R29.P$2 (2), U3.14 (VDDIO), U4.25 (VCC1), U4.26 (AVCC_SUBHS), U4.34 (VCC_USBHS), U4.48 (VCC_USB), U4.61 (VCC(IO)2), U4.84 (VCC(IO)3), U4.97 (VCC(IO)4), U4.110 (VCC(IO)5), U4.123 (VCC(IO)6), U4.138 (VCC(IO)7), U4.149 (VCC(IO)8), U4.154 (VREFH), U4.155 (AVCC0), U4.158 (VREFH0), U4.171 (VCC(IO)9), U6.7 (+VS), U7.7 (+VS), U$2.P19 (VDD)
VDD5: C5.P$1 (1), C6.P$2 (2), C8.P$1 (1), C27.P$1 (1), C28.1, C65.P$1 (1), IC3.3 (OUT), J12.P$2 (5V), J12.P$4 (5V), R1.P$2 (2), R7.P$2 (2), R9.P$1 (1), R12.P$2 (2), R34.P$2 (2), U1.16 (VBUS2), U2.4 (VIN)
VDD_1.2: C45.P$1 (1), C46.P$1 (1), U3.1 (VDD_1.2)
VDD_ENET1: C43.1, C44.P$1 (1), FB2/2.2, U3.2 (VDDA_3.3)
WARNOUT: U4.128 (P1_4), U$2.P9 (WARNOUT)
XCIN: C50.P$1 (1), U4.20 (XCIN), X3.P$1
XCOUT: C51.P$1 (1), U4.21 (XCOUT), X3.P$2
XII: C42.P$1 (1), U3.8 (XI), U$3.1
XOO: C41.P$1 (1), U3.7 (XO), U$3.3
XTAL1: C52.P$1 (1), U4.23 (P2_13/XTAL), X4.1
XTAL2: C53.P$1 (1), U4.24 (P2_12/EXTAL), X4.3
ZX0: U4.135 (P8_2), U$2.P2 (ZX0)
ZX1: U4.134 (P8_1), U$2.P3 (ZX1)
ZX2: U4.133 (P8_0), U$2.P4 (ZX2)

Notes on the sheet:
JTAG

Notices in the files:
parts and their libraries:
COPYRIGHT: Copyright (C) 2018 Accelerated Designs. All rights reserved
COPYRIGHT: Copyright (C) 2023 Ultra Librarian. All rights reserved.
COPYRIGHT: Copyright (C) 2022 Ultra Librarian. All rights reserved.
